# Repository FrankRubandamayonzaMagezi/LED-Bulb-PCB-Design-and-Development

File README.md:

# LED Bulb PCB Design and Development

## Project Overview

This repository documents the design and development of a **5 W, 240 VAC LED bulb PCB**. The project follows the complete engineering workflow from schematic capture and PCB layout to simulation, PCB manufacturing, assembly and hardware testing.

The aim is to design an affordable, reliable and energy-efficient LED bulb suitable for indoor lighting while gaining practical experience in professional PCB design and electronics manufacturing.

---

## Project Objectives

The objectives of this project are to:

- Design a production-ready PCB for a 5 W LED bulb.
- Develop a complete schematic using KiCad.
- Assign footprints to all electronic components.
- Produce a manufacturable PCB layout.
- Simulate the LED bulb power supply using Proteus.
- Generate Gerber files for PCB fabrication.
- Manufacture and assemble the PCB.
- Test and evaluate the final LED bulb.
- Document every stage of the engineering process.

---

## Current Progress

- ✅ Schematic design completed
- ✅ Component footprint assignment completed
- ✅ PCB routing completed
- ✅ 3D PCB verification completed
- ✅ AC-to-DC bridge rectifier simulation completed
- ✅ Gerber generation
- 🔄 PCB fabrication (Training completed- LED bulb PCB fabrication in progress)
- 🔄 Component assembly
- ⏳ Hardware testing
- ⏳ Final product evaluation

---

## Design Specifications

- **Product:** 5 W LED Bulb
- **Input Voltage:** 240 VAC
- **Frequency:** 50 Hz
- **Application:** Indoor Lighting
- **PCB Design Software:** KiCad 10
- **Simulation Software:** Proteus 8 Professional

---

## Skills Demonstrated

This project demonstrates practical experience in:

- PCB schematic capture
- PCB layout design
- Component footprint assignment
- PCB routing
- Electrical Rule Check (ERC)
- Design Rule Check (DRC)
- PCB 3D verification
- Circuit simulation using Proteus
- Power electronics
- PCB fabrication techniques
- Electronics manufacturing
- Git and GitHub version control
- Engineering documentation

---

## Repository Structure

```
LED-Bulb-PCB-Design-and-Development/
│
├── docs/
├── fabrication/
├── footprints/
├── images/
├── pcb/
├── schematic/
├── simulations/
├── symbols/
├── README.md
└── .gitignore
```

---

## Design Workflow

The project follows the following engineering workflow:

1. Component selection
2. Schematic capture
3. Footprint assignment
4. Electrical Rule Check (ERC)
5. PCB layout
6. Component placement
7. PCB routing
8. Design Rule Check (DRC)
9. 3D PCB verification
10. Circuit simulation
11. Gerber generation
12. PCB fabrication
13. PCB assembly
14. Hardware testing
15. Final product evaluation

---

## Components Used

The current design includes:

- MP4050G LED Driver IC
- MB10S Bridge Rectifier
- Fuse
- Electrolytic Capacitors
- Ceramic Capacitors
- Resistors
- LEDs
- AC Input Connector
- PCB Connectors

---

## Proteus Simulation

A Proteus simulation was developed to demonstrate the **AC-to-DC rectification stage** of the LED bulb power supply.

The simulation includes:

- 240 VAC AC source
- Fuse
- Full bridge rectifier
- Electrolytic smoothing capacitor
- Current-limiting resistor
- LED load
- AC voltmeter
- DC voltmeter
- DC ammeter
- Oscilloscope

### Simulation Results

The following measurements were obtained during simulation:

- AC input voltage: **Approximately 241 VAC**
- DC output voltage: **Approximately 338 VDC**
- LED current: **Approximately 4.19 mA**

The simulation confirms successful AC-to-DC conversion and demonstrates the operation of the rectification stage.

> **Note**
>
> The production LED bulb uses the **MP4050G LED Driver IC**. Since a compatible Proteus simulation model is currently unavailable, the simulation focuses on demonstrating the AC-to-DC rectification stage rather than the complete LED driver circuit.

---

## Oscilloscope Waveform Verification

An oscilloscope was connected during the Proteus simulation to observe the AC input and the rectified DC output of the bridge rectifier. The captured waveforms verify the AC-to-DC conversion process by showing the sinusoidal AC input and the rectified DC output before filtering and after filtering. This confirms the correct operation of the bridge rectifier and smoothing capacitor before the power is supplied to the LED load.

---

# Project Gallery

## Schematic Diagram

Complete schematic designed in KiCad.

---

## Initial PCB Layout

First routed PCB layout.

---

## Final PCB Layout

Completed PCB routing ready for Gerber generation and fabrication.

---

## Initial 3D PCB View

Initial 3D visualization.

---

## Final 3D PCB View (Front)

Completed PCB viewed from the component side.

---

## Final 3D PCB View (Back)

Completed PCB viewed from the solder side.

---

## Proteus Simulation

Bridge rectifier simulation demonstrating AC-to-DC conversion.

---

# PCB Fabrication Equipment

The fabrication process involves several specialized machines that support PCB production from raw copper-clad boards to finished printed circuit boards.

The following equipment will be used during the manufacturing process.

---

## PCB Prototyping Process

The PCB prototyping workflow illustrates the sequence of manufacturing steps used to transform the PCB design into a physical circuit board.

---

## Through-Hole PCB

Example of a through-hole PCB used during the fabrication and assembly process.

---

## Through-Hole Drilling Machine

Machine used for drilling component mounting holes after PCB fabrication.

---

## Circuit Board Buffing Machine

Used to clean and polish the PCB surface before and after various fabrication processes, improving surface quality and solderability.

---

## Spray Stripping Machine

Used to remove photoresist after the PCB etching process, leaving the required copper traces on the board.

---

# PCB Fabrication Training

Before manufacturing the LED bulb PCB, practical PCB fabrication techniques were carried out using a **12 V to 5 V Buck Converter** as a training project. This provided hands-on experience with the complete PCB fabrication workflow and the operation of the equipment available in the PCB fabrication laboratory.

The objective was to understand how a PCB progresses from a digital design to a fully fabricated circuit board before applying the same techniques to the LED bulb project.

The fabrication process followed these stages:

- A single-layer copper-clad PCB was selected because the circuit required only one copper layer and no vias.
- The copper surface was thoroughly cleaned to remove contaminants and improve toner adhesion.
- The PCB layout was printed onto transfer paper and transferred onto the copper-clad board using the toner transfer method with heat and pressure.
- The board was immersed in Ferric Chloride solution to chemically etch away the exposed copper, leaving only the required PCB traces protected by the toner.
- The remaining toner was removed using ethanol, exposing clean copper tracks on the FR4 substrate.
- The fabricated PCB was then prepared for the remaining finishing processes, including drilling, solder mask application and silkscreen printing.

This practical exercise provided valuable experience in PCB fabrication techniques, chemical etching, surface preparation and manufacturing processes that will be applied during the fabrication of the 5 W LED bulb PCB developed in this repository.

## From Digital Design to Copper-Clad Board

The PCB fabrication process began by preparing a clean copper-clad board while referencing the digital PCB layout. This marked the transition from the computer-aided PCB design to the physical manufacturing process.

---

## PCB with Toner Transfer

The PCB layout was transferred onto the cleaned copper-clad board using the toner transfer method. The toner formed a protective layer over the required copper traces before chemical etching.

---

## Ferric Chloride Etching

The board was immersed in a Ferric Chloride solution to dissolve the exposed copper while preserving the toner-protected PCB traces.

---

## PCB after Toner Removal

After chemical etching, the toner was removed using ethanol to expose the finished copper traces on the FR4 substrate. At this stage, the PCB pattern was fully formed and ready for drilling.

---

## PCB Drilling

Component mounting holes were drilled at the required locations using a PCB drilling machine, preparing the board for component placement and soldering.

---

## Heat Press Machine

A heat press machine was used during the toner transfer process to firmly bond the printed PCB artwork onto the copper-clad board. Proper heat and pressure ensured accurate transfer of the circuit pattern before chemical etching.

---
After chemical etching, the remaining toner was removed using ethanol to expose the finished copper traces on the FR4 substrate. At this stage, the PCB pattern had been successfully transferred onto the board and was ready for the remaining manufacturing processes.

The subsequent fabrication stages typically include:

- PCB drilling for through-hole components and mounting holes
- Surface cleaning and inspection
- Tin coating or surface finishing (where applicable) to protect exposed copper
- Solder mask application to insulate and protect the copper traces from oxidation and accidental short circuits
- Silkscreen printing to add component labels, reference designators and other markings
- Electrical continuity and quality inspection
- Component assembly and soldering
- Functional testing of the completed PCB

These finishing processes transform the etched PCB into a fully assembled and production-ready electronic circuit.
---

## Engineering Considerations

During the PCB design process, attention was given to:

- Proper component placement
- Efficient PCB routing
- Trace spacing
- Design for Manufacturability (DFM)
- Electrical Rule Check (ERC)
- Design Rule Check (DRC)
- PCB inspection using the KiCad 3D Viewer

---

## Future Work

The remaining stages of the project include:

- Generate Gerber files
- Manufacture the PCB
- Assemble the LED bulb
- Perform electrical testing
- Measure efficiency
- Evaluate thermal performance
- Produce final engineering documentation

---

## Learning Outcomes

Working on this project has provided practical experience in:

- PCB design using KiCad
- Circuit simulation using Proteus
- PCB routing techniques
- Power electronics
- Electronics manufacturing workflow
- Git and GitHub
- Engineering documentation

## License

This repository is shared for educational and portfolio purposes.

Please contact the repository owner before using any part of this design for commercial applications.

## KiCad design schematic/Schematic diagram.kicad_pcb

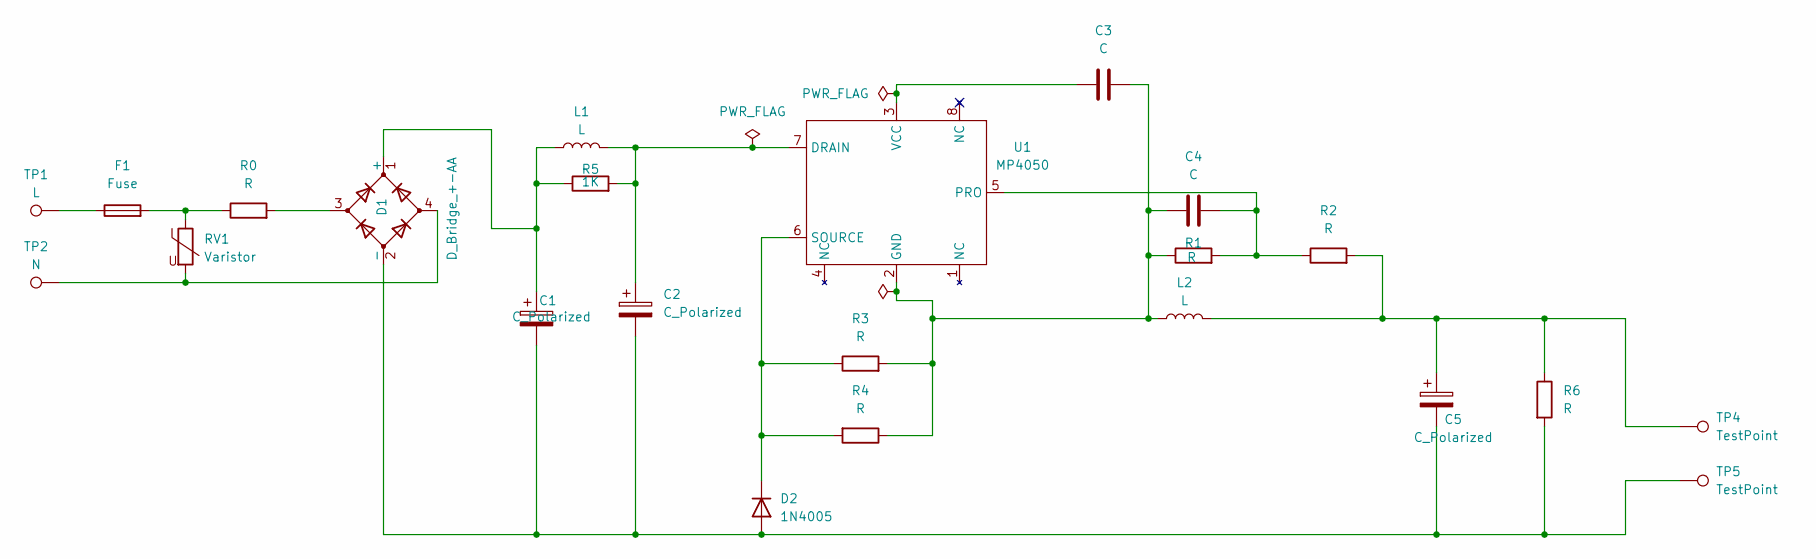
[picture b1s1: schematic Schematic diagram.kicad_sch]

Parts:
C1, C2: C_Polarized; CP_Radial_D8.0mm_P5.00mm
C3: C; C_Disc_D5.0mm_W2.5mm_P2.50mm
C4: C; C_Disc_D3.0mm_W1.6mm_P2.50mm
C5: C_Polarized; CP_Radial_D5.0mm_P2.00mm
D1: D_Bridge_+-AA; Diode_Bridge_Diotec_ABS
D2: 1N4005; D_SMA
F1: Fuse; Fuse_Bourns_MF-RG300
L1, L2: L; L_Radial_D6.0mm_P4.00mm
R0: R; R_Axial_DIN0204_L3.6mm_D1.6mm_P7.62mm_Horizontal
R1, R6: R; R_0603_1608Metric
R2, R3, R4: R; R_1206_3216Metric
R5: 1K; R_1206_3216Metric
RV1: Varistor; RV_Disc_D7mm_W4mm_P5mm
TP1: L; TestPoint_THTPad_2.0x2.0mm_Drill1.0mm
TP2: N; TestPoint_THTPad_2.0x2.0mm_Drill1.0mm
TP4, TP5: TestPoint; TestPoint_THTPad_2.0x2.0mm_Drill1.0mm
U1: MP4050; SOIC127P600X175-8N

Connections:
unnamed: C5.1, L2.2, R2.2, R6.1, TP4.1 (1_1)
unnamed: C1.1, D1.1 (+), L1.1, R5.1
unnamed: C1.2, C2.2, C5.2, D1.2 (-), D2.2 (A), R6.2, TP5.1 (1_1)
unnamed: D1.3, R0.2
unnamed: D1.4, RV1.2, TP2.1 (1_1)
unnamed: D2.1 (K), R3.1, R4.2, U1.6 (SOURCE)
unnamed: F1.1, TP1.1 (1_1)
unnamed: F1.2, R0.1, RV1.1
unnamed: C2.1, L1.2, R5.2, U1.7 (DRAIN)
unnamed: C3.2, C4.1, L2.1, R1.1, R3.2, R4.1, U1.2 (GND)
unnamed: C4.2, R1.2, R2.1, U1.5 (PRO)
unnamed: C3.1, U1.3 (VCC)

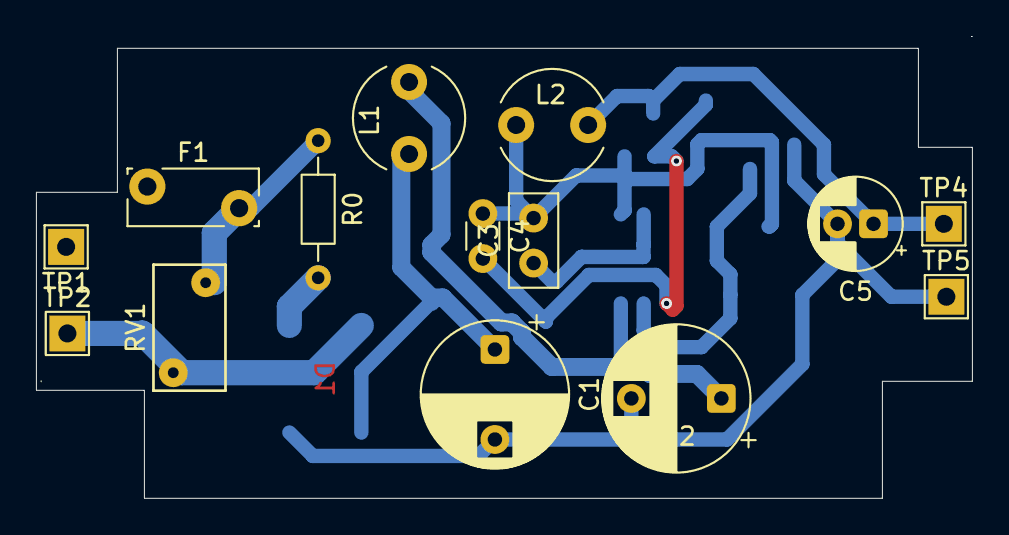
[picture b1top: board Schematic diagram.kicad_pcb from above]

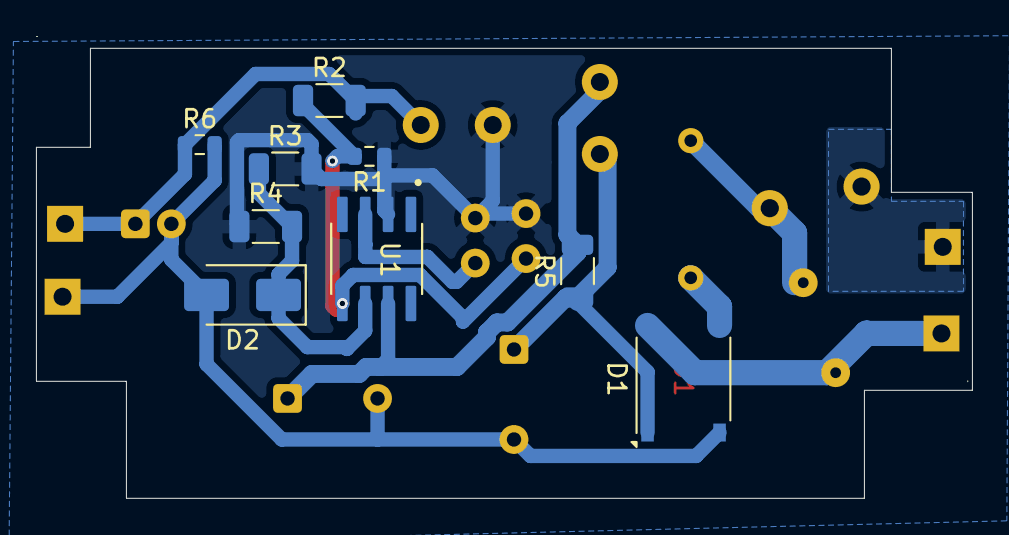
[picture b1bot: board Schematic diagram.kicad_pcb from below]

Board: 2 copper layers, 52.0 x 25.7 mm, 23 parts (9 on the bottom side), 12 nets.
